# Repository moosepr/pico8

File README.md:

# pico8
a handheld pico-8 player

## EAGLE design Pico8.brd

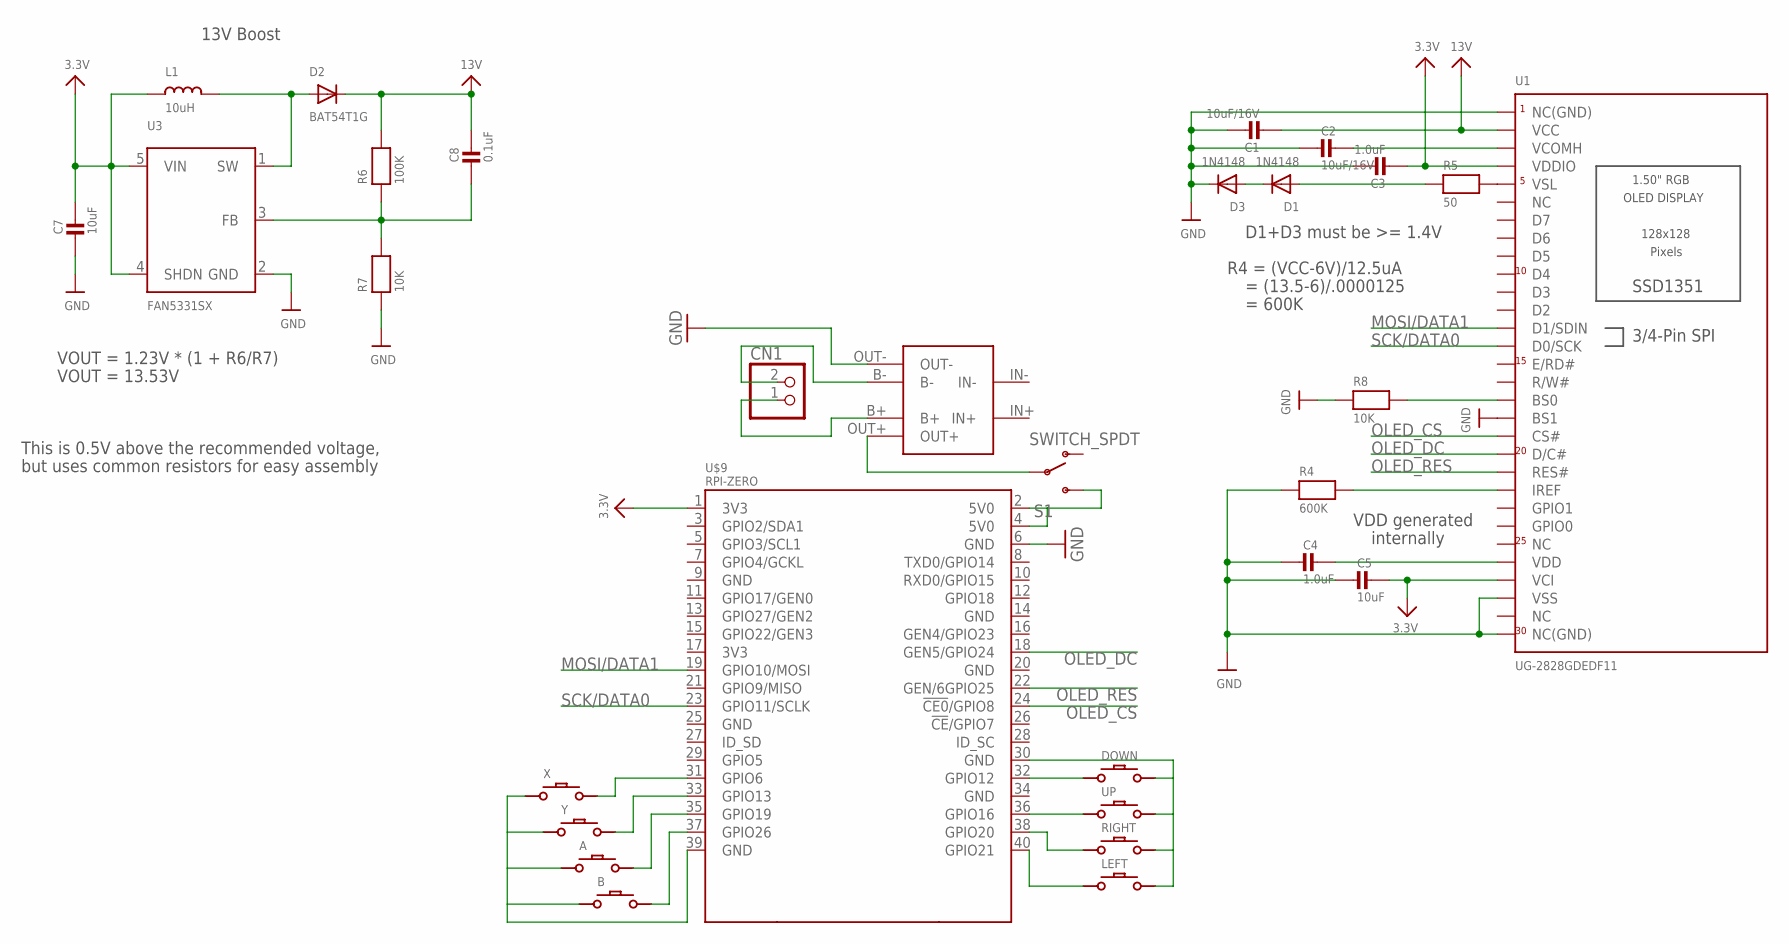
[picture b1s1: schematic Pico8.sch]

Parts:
A: DMG-BTNREGULAR; DMG-BTN
B: DMG-BTNREGULAR; DMG-BTN
C1, C2: 10uF/16V; 0805
C3, C4: 1.0uF; 0805
C5, C7: 10uF; 0805
C8: 0.1uF; 0805
CN1: JST_2PIN-SMT-RA; JST-PH-2-SMT-RA
D1, D3: 1N4148; SOD-323
D2: BAT54T1G; SOD-123
DOWN: DMG-BTNREGULAR; DMG-BTN
L1: 10uH; INDUCTOR_1007
LEFT: DMG-BTNREGULAR; DMG-BTN
POWER1: 03962A
R4: 600K; 0805
R5: 50; 0805
R6: 100K; 0805
R7, R8: 10K; 0805
RIGHT: DMG-BTNREGULAR; DMG-BTN
S1: SWITCH_SPDT; KPS-1290
U1: UG-2828GDEDF11; FPC_XF2M-3015-1A
U3: FAN5331SX; SOT23-5@1
U$9: RPI-ZERO; RASPBERRYPI_BASTELSTUBE_V13_RASPI_BOARD_B+_FULL
UP: DMG-BTNREGULAR; DMG-BTN
X: DMG-BTNREGULAR; DMG-BTN
Y: DMG-BTNREGULAR; DMG-BTN

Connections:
3.3V: C3.2, C5.1, C7.1, L1.P$1 (1), U1.P$4 (VCI), U1.P$27 (VDDIO), U3.4 (SHDN), U3.5 (VIN)
3V3@1: U$9.1 (3V3)
5V0@2: S1.S, U$9.2 (5V0), U$9.4 (5V0)
13V: C1.2, C8.1, D2.C, R6.2, U1.P$29 (VCC)
GND: C1.1, C2.2, C3.1, C4.2, C5.2, C7.2, D3.C, POWER1.OUT-, R4.1, R7.1, R8.1, U1.P$1 (NC(GND)), U1.P$3 (VSS), U1.P$13 (BS1), U1.P$30 (NC(GND)), U3.2 (GND)
GND@3: A.P$1, B.P$1, U$9.39 (GND), X.P$1, Y.P$1
GND@6: DOWN.P$2, LEFT.P$2, RIGHT.P$2, U$9.30 (GND), UP.P$2
GND@8: U$9.6 (GND)
IREF: R4.2, U1.P$9 (IREF)
MOSI/DATA1: U1.P$18 (D1/SDIN), U$9.19 (GPIO10/MOSI)
unnamed: R8.2, U1.P$14 (BS0)
unnamed: POWER1.OUT+, S1.P
unnamed: C4.1, U1.P$5 (VDD)
unnamed: D2.A, L1.P$2 (2), U3.1 (SW)
unnamed: R5.2, U1.P$26 (VSL)
unnamed: D1.A, R5.1
unnamed: C8.2, R6.1, R7.2, U3.3 (FB)
unnamed: D1.C, D3.A
unnamed: LEFT.P$1, U$9.40 (GPIO21)
unnamed: RIGHT.P$1, U$9.38 (GPIO20)
unnamed: U$9.36 (GPIO16), UP.P$1
unnamed: DOWN.P$1, U$9.32 (GPIO12)
unnamed: B.P$2, U$9.37 (GPIO26)
unnamed: A.P$2, U$9.35 (GPIO19)
unnamed: U$9.33 (GPIO13), Y.P$2
unnamed: U$9.31 (GPIO6), X.P$2
unnamed: CN1.1 (2), POWER1.B+
unnamed: CN1.2 (1), POWER1.B-
OLED_CS: U1.P$12 (CS#), U$9.24 (!CE0!/GPIO8)
OLED_DC: U1.P$11 (D/C#), U$9.18 (GEN5/GPIO24)
OLED_RES: U1.P$10 (RES#), U$9.22 (GEN/6GPIO25)
SCK/DATA0: U1.P$17 (D0/SCK), U$9.23 (GPIO11/SCLK)
VCOMH: C2.1, U1.P$28 (VCOMH)

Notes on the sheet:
VOUT = 1.23V * (1 + R6/R7)
VOUT = 13.53V
This is 0.5V above the recommended voltage,
but uses common resistors for easy assembly
13V Boost
R4 = (VCC-6V)/12.5uA
= (13.5-6)/.0000125
= 600K
D1+D3 must be >= 1.4V
VDD generated
internally

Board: 2 copper layers, 30 parts (22 on the bottom side), 31 nets, no tracks yet.

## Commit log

2017-11-15 Add files via upload
    initial commit

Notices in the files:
parts and their libraries:
SparkFun-Electromechanical: Licensing: Creative Commons ShareAlike 4.0 International - https://creativecommons.org/licenses/by-sa/4.0
